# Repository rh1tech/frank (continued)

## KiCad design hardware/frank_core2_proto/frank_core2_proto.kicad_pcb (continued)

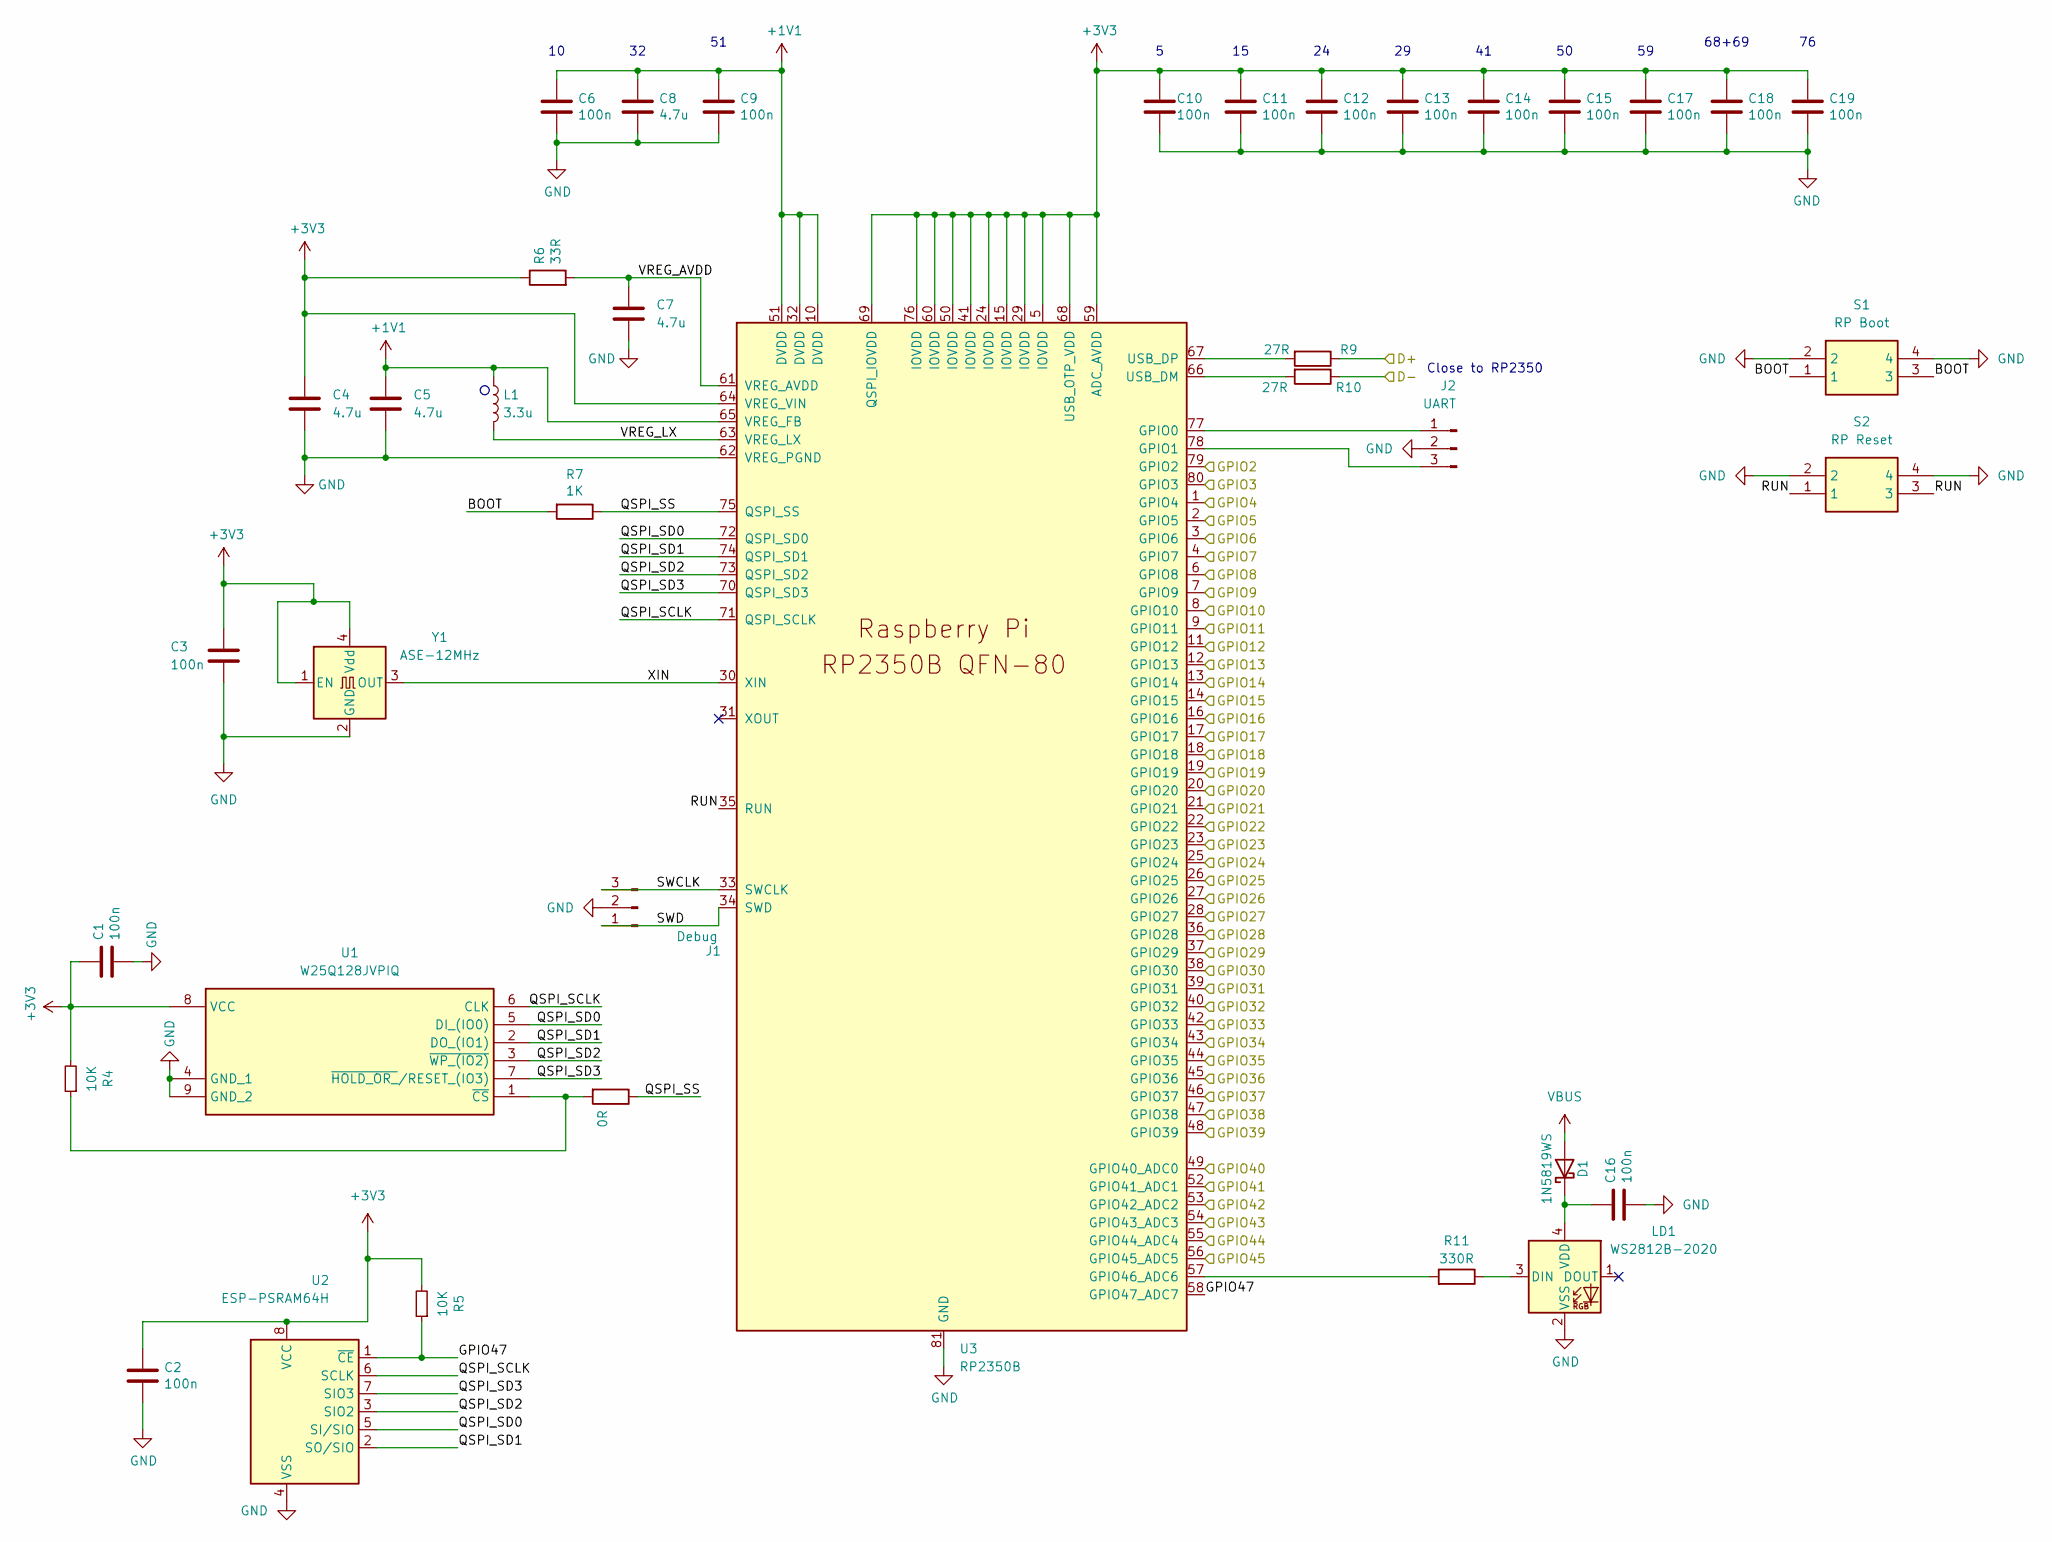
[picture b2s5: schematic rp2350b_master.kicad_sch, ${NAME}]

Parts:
C1, C2, C3, C6, C9, C10, C11, C12, C13, C14, C15, C16, C17, C18, C19: 100n; C_0603_1608Metric
C4, C5, C7, C8: 4.7u; C_0603_1608Metric
D1: 1N5819WS; D_SOD-323
J1: Debug; JST_SH_1x03_P1.00mm_Vertical
J2: UART; JST_SH_1x03_P1.00mm_Vertical
L1: 3.3u; L_Murata_LQH2MCN_2.0x1.6mm
LD1: WS2812B-2020; LED_WS2812B-2020_PLCC4_2.0x2.0mm
R4, R5: 10K; R_0603_1608Metric
R6: 33R; R_0603_1608Metric
R7: 1K; R_0603_1608Metric
R8: 0R; R_0603_1608Metric
R9, R10: 27R; R_0603_1608Metric
R11: 330R; R_0603_1608Metric
S1: RP Boot; SW_SPST_KMR2; Mouser Part Number 611-KMR221G-LFS
S2: RP Reset; SW_SPST_KMR2; Mouser Part Number 611-KMR221G-LFS
U1: W25Q128JVPIQ; WSON-8-1EP_6x5mm_P1.27mm_EP3.45x4.35mm; Mouser Part Number 454-W25Q128JVPIQ
U2: ESP-PSRAM64H; SOIC-8_3.9x4.9mm_P1.27mm
U3: RP2350B; QFN-80-1EP_10x10mm_P0.4mm_EP3.4x3.4mm
Y1: ASE-12MHz; Oscillator_SMD_3225-4Pin_3.2x2.5mm

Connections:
+1V1: C5.1, C6.1, C8.1, C9.1, L1.1, U3.10 (DVDD), U3.32 (DVDD), U3.51 (DVDD), U3.65 (VREG_FB)
+3V3: C1.1, C2.1, C3.1, C4.1, C10.1, C11.1, C12.1, C13.1, C14.1, C15.1, C17.1, C18.1, C19.1, R4.2, R5.2, R6.1, U1.8 (VCC), U2.8 (VCC), U3.5 (IOVDD), U3.15 (IOVDD), U3.24 (IOVDD), U3.29 (IOVDD), U3.41 (IOVDD), U3.50 (IOVDD), U3.59 (ADC_AVDD), U3.60 (IOVDD), U3.64 (VREG_VIN), U3.68 (USB_OTP_VDD), U3.69 (QSPI_IOVDD), U3.76 (IOVDD), Y1.1 (EN), Y1.4 (Vdd); also elsewhere on the board
/HDMI/CLKN/GPIO12: U3.11 (GPIO12); also elsewhere on the board
/HDMI/CLKP/GPIO13: U3.12 (GPIO13); also elsewhere on the board
/HDMI/D0N/GPIO14: U3.13 (GPIO14); also elsewhere on the board
/HDMI/D0P/GPIO15: U3.14 (GPIO15); also elsewhere on the board
/HDMI/D1N/GPIO16: U3.16 (GPIO16); also elsewhere on the board
/HDMI/D1P/GPIO17: U3.17 (GPIO17); also elsewhere on the board
/HDMI/D2N/GPIO18: U3.18 (GPIO18); also elsewhere on the board
/HDMI/D2P/GPIO19: U3.19 (GPIO19); also elsewhere on the board
/RP2350B/BOOT: R7.2, S1.1, S1.3
/RP2350B/GPIO2: U3.79 (GPIO2)
/RP2350B/GPIO3: U3.80 (GPIO3)
/RP2350B/GPIO8: U3.6 (GPIO8)
/RP2350B/GPIO28: U3.36 (GPIO28); also elsewhere on the board
/RP2350B/GPIO44: U3.55 (GPIO44_ADC4)
/RP2350B/GPIO45: U3.56 (GPIO45_ADC5)
/RP2350B/GPIO47: R5.1, U2.1 (~CE), U3.58 (GPIO47_ADC7)
/RP2350B/QSPI_SCLK: U1.6 (CLK), U2.6 (SCLK), U3.71 (QSPI_SCLK)
/RP2350B/QSPI_SD0: U1.5 (DI_(IO0)), U2.5 (SI/SIO), U3.72 (QSPI_SD0)
/RP2350B/QSPI_SD1: U1.2 (DO_(IO1)), U2.2 (SO/SIO), U3.74 (QSPI_SD1)
/RP2350B/QSPI_SD2: U1.3 (~WP_(IO2)), U2.3 (SIO2), U3.73 (QSPI_SD2)
/RP2350B/QSPI_SD3: U1.7 (~HOLD_OR_/RESET_(IO3)), U2.7 (SIO3), U3.70 (QSPI_SD3)
/RP2350B/QSPI_SS: R7.1, R8.1, U3.75 (QSPI_SS)
/RP2350B/RUN: S2.1, S2.3, U3.35 (RUN)
/RP2350B/SWCLK: J1.3, U3.33 (SWCLK)
/RP2350B/SWD: J1.1, U3.34 (SWD)
/RP2350B/VREG_AVDD: C7.1, R6.2, U3.61 (VREG_AVDD)
/RP2350B/VREG_LX: L1.2, U3.63 (VREG_LX)
/RP2350B/XIN: U3.30 (XIN), Y1.3 (OUT)
/RP2350B/D+: R9.1; also elsewhere on the board
/RP2350B/D-: R10.1; also elsewhere on the board
/RP2350/20B/1A/D0: U3.20 (GPIO20); also elsewhere on the board
/RP2350/21B/2A/D1: U3.21 (GPIO21); also elsewhere on the board
/RP2350/22B/3A/D2: U3.22 (GPIO22); also elsewhere on the board
/RP2350/23B/4A/D3: U3.23 (GPIO23); also elsewhere on the board
/RP2350/24B/5A/D4: U3.25 (GPIO24); also elsewhere on the board
/RP2350/25B/6A/D5: U3.26 (GPIO25); also elsewhere on the board
/RP2350/26B/7A/D6: U3.27 (GPIO26); also elsewhere on the board
/RP2350/27B/8A/D7: U3.28 (GPIO27); also elsewhere on the board
/RP2350/29B/10A/VALID: U3.37 (GPIO29); also elsewhere on the board
/RP2350/30B/11A/D0: U3.38 (GPIO30); also elsewhere on the board
/RP2350/31B/12A/D1: U3.39 (GPIO31); also elsewhere on the board
/RP2350/32B/13A/D2: U3.40 (GPIO32); also elsewhere on the board
/RP2350/33B/14A/D3: U3.42 (GPIO33); also elsewhere on the board
/RP2350/34B/15A/D4: U3.43 (GPIO34); also elsewhere on the board
/RP2350/35B/16A/D5: U3.44 (GPIO35); also elsewhere on the board
/RP2350/36B/17A/D6: U3.45 (GPIO36); also elsewhere on the board
/RP2350/37B/18A/D7: U3.46 (GPIO37); also elsewhere on the board
/RP2350/38B/19A/CLK: U3.47 (GPIO38); also elsewhere on the board
/RP2350/39B/20A/VALID: U3.48 (GPIO39); also elsewhere on the board
/RP2350/40B/21A/FS: U3.49 (GPIO40_ADC0); also elsewhere on the board
/RP2350/41B/22A/DB_MS: U3.52 (GPIO41_ADC1); also elsewhere on the board
/RP2350/42B/23A/DB_SM: U3.53 (GPIO42_ADC2); also elsewhere on the board
/RP2350/43B/RUNA/SR: U3.54 (GPIO43_ADC3); also elsewhere on the board
/SD/CDDAT3/GPIO5: U3.2 (GPIO5); also elsewhere on the board
/SD/CLK/GPIO6: U3.3 (GPIO6); also elsewhere on the board
/SD/CMD/GPIO7: U3.4 (GPIO7); also elsewhere on the board
/SD/DAT0/GPIO4: U3.1 (GPIO4); also elsewhere on the board
/TDA/DATA/GPIO9: U3.7 (GPIO9); also elsewhere on the board
/TDA/LRCK/GPIO11: U3.9 (GPIO11); also elsewhere on the board
/TDA/SCLK/GPIO10: U3.8 (GPIO10); also elsewhere on the board
GND: C1.2, C2.2, C3.2, C4.2, C5.2, C6.2, C7.2, C8.2, C9.2, C10.2, C11.2, C12.2, C13.2, C14.2, C15.2, C16.2, C17.2, C18.2, C19.2, J1.2, J2.2, LD1.2 (VSS), S1.2, S1.4, S2.2, S2.4, U1.4 (GND_1), U1.9 (GND_2), U2.4 (VSS), U3.62 (VREG_PGND), U3.81 (GND), Y1.2 (GND); also elsewhere on the board
unnamed: C16.1, D1.1 (K), LD1.4 (VDD)
unnamed: J2.1, U3.77 (GPIO0)
unnamed: J2.3, U3.78 (GPIO1)
unnamed: LD1.3 (DIN), R11.1
unnamed: R4.1, R8.2, U1.1 (~CS)
unnamed: R11.2, U3.57 (GPIO46_ADC6)
unnamed: R10.2, U3.66 (USB_DM)
unnamed: R9.2, U3.67 (USB_DP)
VBUS: D1.2 (A); also elsewhere on the board

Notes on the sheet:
Close to RP2350
68+69

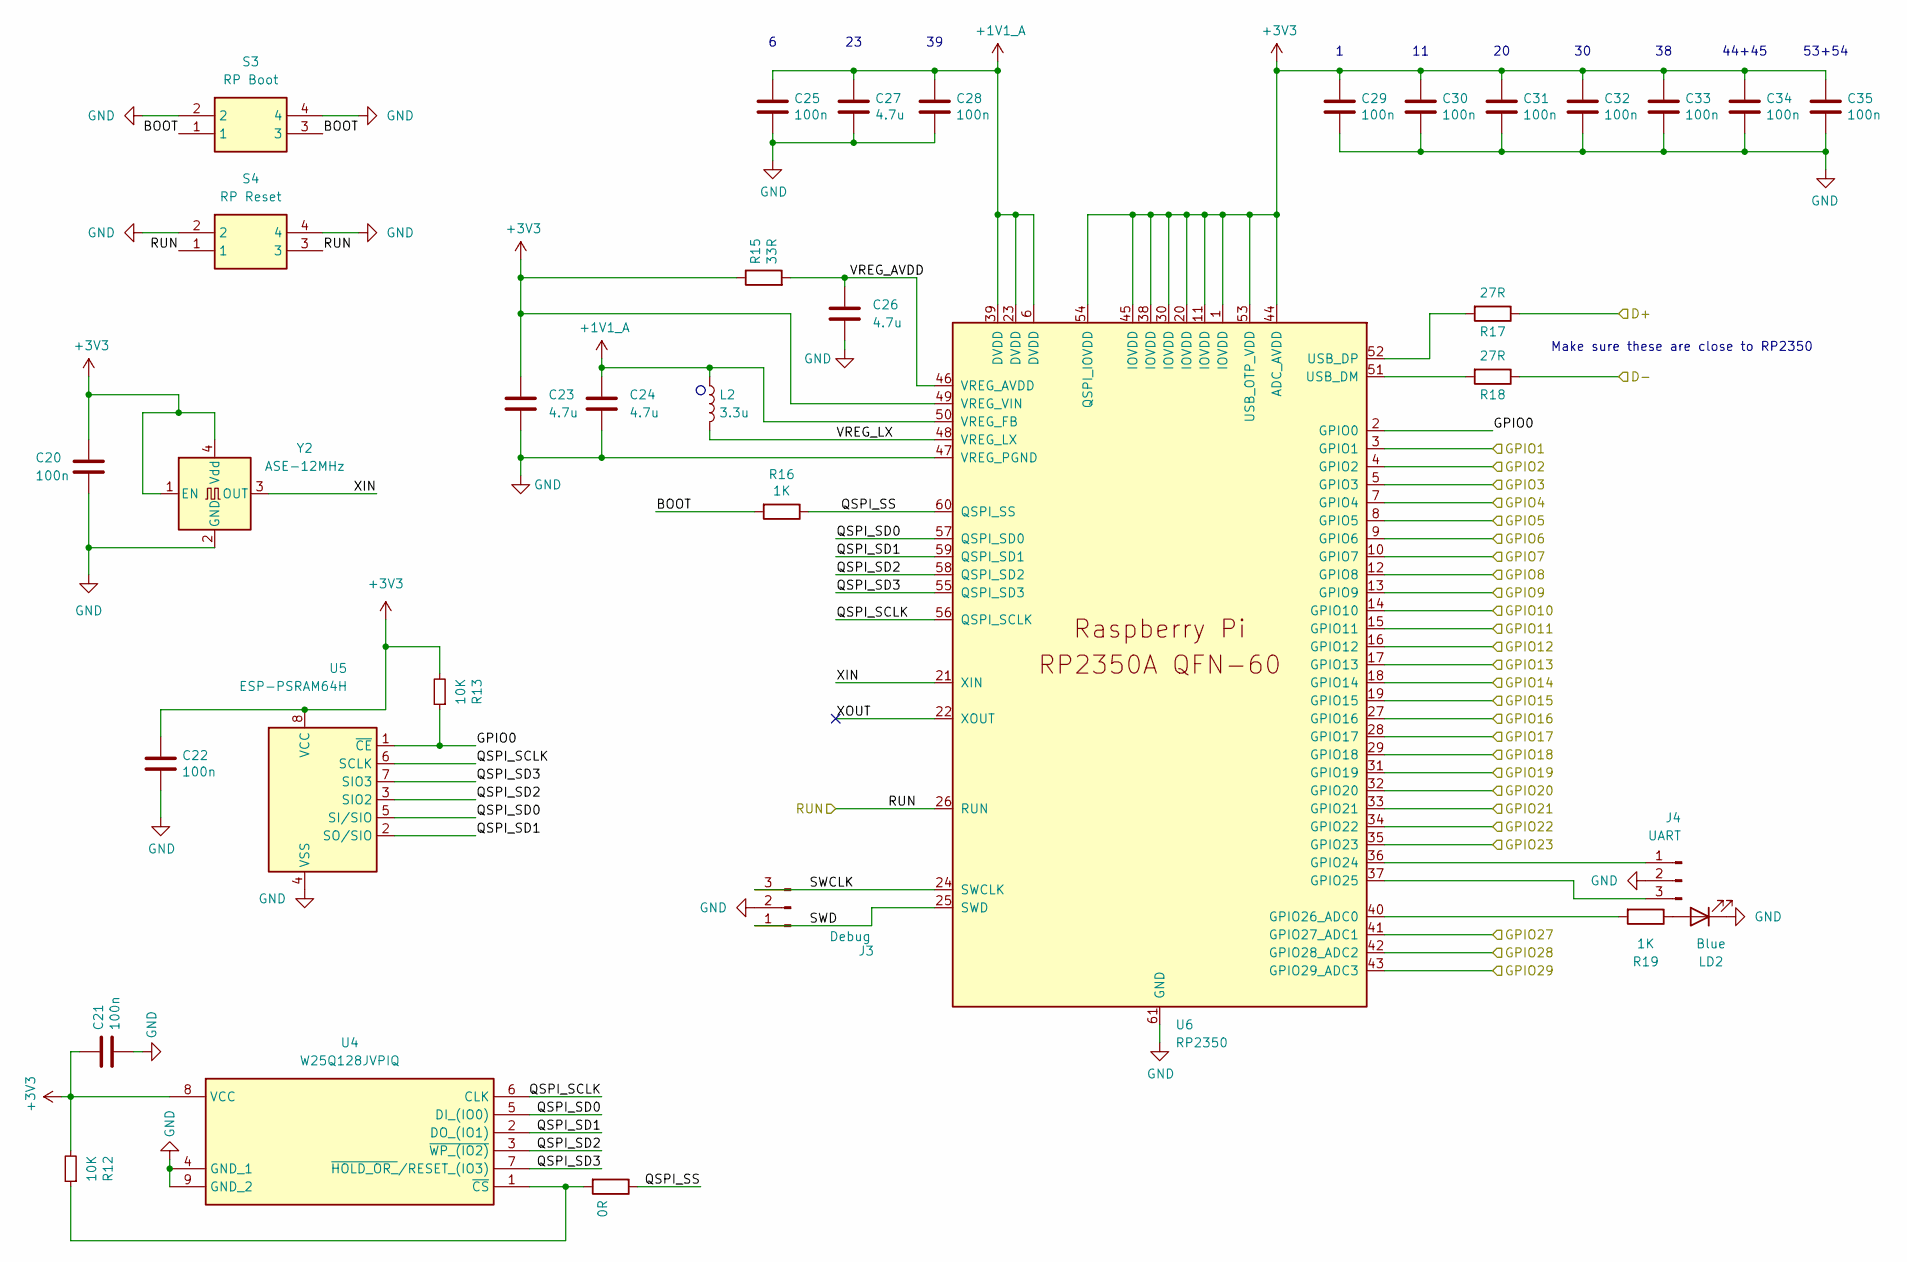
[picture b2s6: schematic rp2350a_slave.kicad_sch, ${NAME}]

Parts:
C20, C21, C22, C25, C28, C29, C30, C31, C32, C33, C34, C35: 100n; C_0603_1608Metric
C23, C24, C26, C27: 4.7u; C_0603_1608Metric
J3: Debug; JST_SH_1x03_P1.00mm_Vertical
J4: UART; JST_SH_1x03_P1.00mm_Vertical
L2: 3.3u; L_AOTA-B201610_2.0x1.6mm
LD2: Blue; LED_0603_1608Metric
R12, R13: 10K; R_0603_1608Metric
R14: 0R; R_0603_1608Metric
R15: 33R; R_0603_1608Metric
R16, R19: 1K; R_0603_1608Metric
R17, R18: 27R; R_0603_1608Metric
S3: RP Boot; SW_SPST_KMR2; Mouser Part Number 611-KMR221G-LFS
S4: RP Reset; SW_SPST_KMR2; Mouser Part Number 611-KMR221G-LFS
U4: W25Q128JVPIQ; WSON-8-1EP_6x5mm_P1.27mm_EP3.45x4.35mm; Mouser Part Number 454-W25Q128JVPIQ
U5: ESP-PSRAM64H; SOIC-8_3.9x4.9mm_P1.27mm
U6: RP2350; QFN-60-1EP_7x7mm_P0.4mm_EP3.4x3.4mm
Y2: ASE-12MHz; Oscillator_SMD_Abracon_ASE-4Pin_3.2x2.5mm

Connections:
+1V1_A: C24.1, C25.1, C27.1, C28.1, L2.1, U6.6 (DVDD), U6.23 (DVDD), U6.39 (DVDD), U6.50 (VREG_FB)
+3V3: C20.1, C21.1, C22.1, C23.1, C29.1, C30.1, C31.1, C32.1, C33.1, C34.1, C35.1, R12.2, R13.2, R15.1, U4.8 (VCC), U5.8 (VCC), U6.1 (IOVDD), U6.11 (IOVDD), U6.20 (IOVDD), U6.30 (IOVDD), U6.38 (IOVDD), U6.44 (ADC_AVDD), U6.45 (IOVDD), U6.49 (VREG_VIN), U6.53 (USB_OTP_VDD), U6.54 (QSPI_IOVDD), Y2.1 (EN), Y2.4 (Vdd); also elsewhere on the board
/RP2350A/BOOT: R16.2, S3.1, S3.3
/RP2350A/GPIO0: R13.1, U5.1 (~CE), U6.2 (GPIO0)
/RP2350A/GPIO19: U6.31 (GPIO19); also elsewhere on the board
/RP2350A/GPIO27: U6.41 (GPIO27_ADC1)
/RP2350A/GPIO28: U6.42 (GPIO28_ADC2)
/RP2350A/GPIO29: U6.43 (GPIO29_ADC3)
/RP2350A/QSPI_SCLK: U4.6 (CLK), U5.6 (SCLK), U6.56 (QSPI_SCLK)
/RP2350A/QSPI_SD0: U4.5 (DI_(IO0)), U5.5 (SI/SIO), U6.57 (QSPI_SD0)
/RP2350A/QSPI_SD1: U4.2 (DO_(IO1)), U5.2 (SO/SIO), U6.59 (QSPI_SD1)
/RP2350A/QSPI_SD2: U4.3 (~WP_(IO2)), U5.3 (SIO2), U6.58 (QSPI_SD2)
/RP2350A/QSPI_SD3: U4.7 (~HOLD_OR_/RESET_(IO3)), U5.7 (SIO3), U6.55 (QSPI_SD3)
/RP2350A/QSPI_SS: R14.1, R16.1, U6.60 (QSPI_SS)
/RP2350A/SWCLK: J3.3, U6.24 (SWCLK)
/RP2350A/SWD: J3.1, U6.25 (SWD)
/RP2350A/VREG_AVDD: C26.1, R15.2, U6.46 (VREG_AVDD)
/RP2350A/VREG_LX: L2.2, U6.48 (VREG_LX)
/RP2350A/XIN: U6.21 (XIN), Y2.3 (OUT)
/RP2350A/XOUT: U6.22 (XOUT)
/RP2350A/D+: R17.1; also elsewhere on the board
/RP2350A/D-: R18.1; also elsewhere on the board
/RP2350/20B/1A/D0: U6.3 (GPIO1); also elsewhere on the board
/RP2350/21B/2A/D1: U6.4 (GPIO2); also elsewhere on the board
/RP2350/22B/3A/D2: U6.5 (GPIO3); also elsewhere on the board
/RP2350/23B/4A/D3: U6.7 (GPIO4); also elsewhere on the board
/RP2350/24B/5A/D4: U6.8 (GPIO5); also elsewhere on the board
/RP2350/25B/6A/D5: U6.9 (GPIO6); also elsewhere on the board
/RP2350/26B/7A/D6: U6.10 (GPIO7); also elsewhere on the board
/RP2350/27B/8A/D7: U6.12 (GPIO8); also elsewhere on the board
/RP2350/28B/9A/CLK: U6.13 (GPIO9); also elsewhere on the board
/RP2350/29B/10A/VALID: U6.14 (GPIO10); also elsewhere on the board
/RP2350/30B/11A/D0: U6.15 (GPIO11); also elsewhere on the board
/RP2350/31B/12A/D1: U6.16 (GPIO12); also elsewhere on the board
/RP2350/32B/13A/D2: U6.17 (GPIO13); also elsewhere on the board
/RP2350/33B/14A/D3: U6.18 (GPIO14); also elsewhere on the board
/RP2350/34B/15A/D4: U6.19 (GPIO15); also elsewhere on the board
/RP2350/35B/16A/D5: U6.27 (GPIO16); also elsewhere on the board
/RP2350/36B/17A/D6: U6.28 (GPIO17); also elsewhere on the board
/RP2350/37B/18A/D7: U6.29 (GPIO18); also elsewhere on the board
/RP2350/39B/20A/VALID: U6.32 (GPIO20); also elsewhere on the board
/RP2350/40B/21A/FS: U6.33 (GPIO21); also elsewhere on the board
/RP2350/41B/22A/DB_MS: U6.34 (GPIO22); also elsewhere on the board
/RP2350/42B/23A/DB_SM: U6.35 (GPIO23); also elsewhere on the board
/RP2350/43B/RUNA/SR: S4.1, S4.3, U6.26 (RUN); also elsewhere on the board
GND: C20.2, C21.2, C22.2, C23.2, C24.2, C25.2, C26.2, C27.2, C28.2, C29.2, C30.2, C31.2, C32.2, C33.2, C34.2, C35.2, J3.2, J4.2, LD2.1 (K), S3.2, S3.4, S4.2, S4.4, U4.4 (GND_1), U4.9 (GND_2), U5.4 (VSS), U6.47 (VREG_PGND), U6.61 (GND), Y2.2 (GND); also elsewhere on the board
unnamed: J4.1, U6.36 (GPIO24)
unnamed: J4.3, U6.37 (GPIO25)
unnamed: LD2.2 (A), R19.1
unnamed: R12.1, R14.2, U4.1 (~CS)
unnamed: R19.2, U6.40 (GPIO26_ADC0)
unnamed: R18.2, U6.51 (USB_DM)
unnamed: R17.2, U6.52 (USB_DP)

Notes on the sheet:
44+45
Make sure these are close to RP2350
53+54

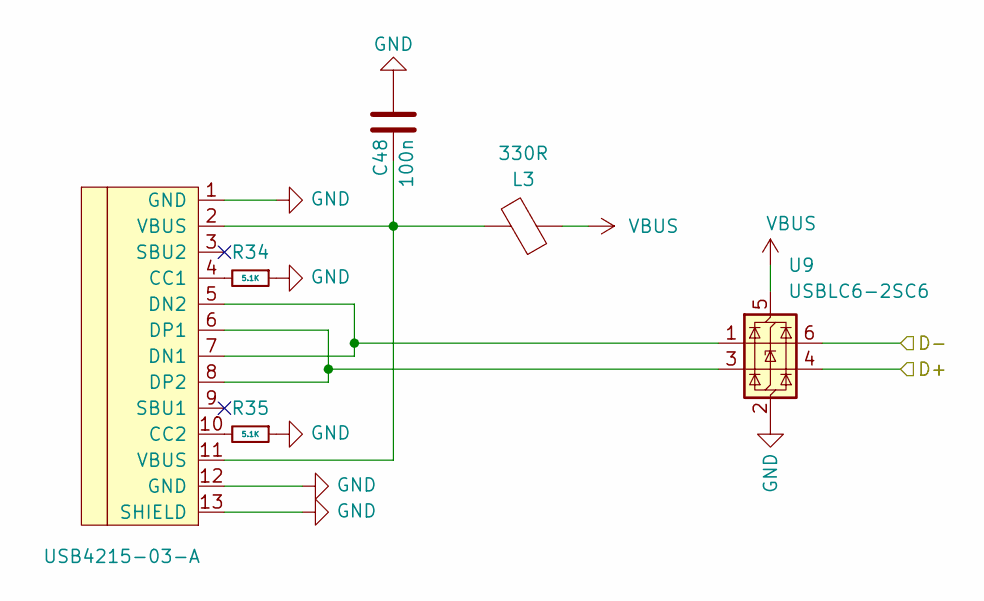
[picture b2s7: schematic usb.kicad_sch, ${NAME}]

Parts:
C48: 100n; C_0603_1608Metric
J8: USB4215-03-A; USB_C_Receptacle; LCSC C165948
L3: 330R; L_0603_1608Metric
R34, R35: 5.1K; R_0603_1608Metric
U9: USBLC6-2SC6; SOT-23-6

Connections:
/RP2350B/D+: U9.4 (I/O2); also elsewhere on the board
/RP2350B/D-: U9.6 (I/O1); also elsewhere on the board
GND: C48.2, J8.1 (GND), J8.12 (GND), J8.13 (SHIELD), R34.1, R35.1, U9.2 (GND); also elsewhere on the board
unnamed: C48.1, J8.2 (VBUS), J8.11 (VBUS), L3.2
unnamed: J8.4 (CC1), R34.2
unnamed: J8.10 (CC2), R35.2
unnamed: J8.5 (DN2), J8.7 (DN1), U9.1 (I/O1)
unnamed: J8.6 (DP1), J8.8 (DP2), U9.3 (I/O2)
VBUS: L3.1, U9.5 (VBUS); also elsewhere on the board

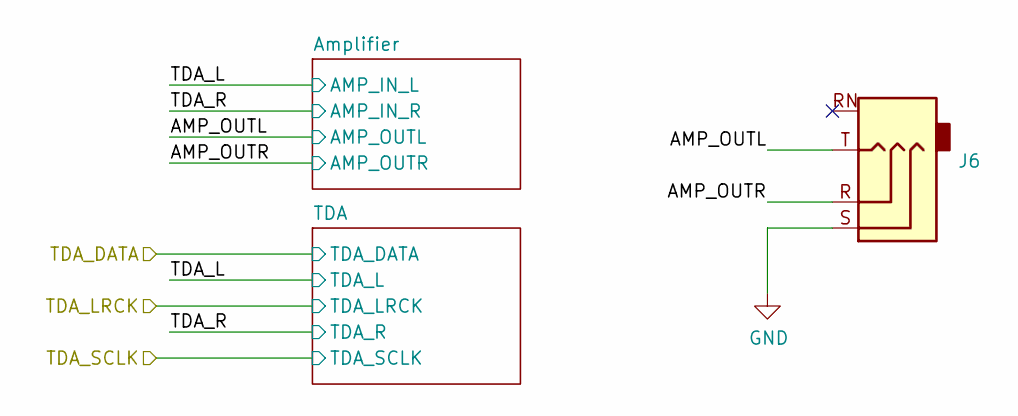
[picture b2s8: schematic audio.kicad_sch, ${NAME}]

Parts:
J6: PJ-320D; AudioJack_3.5mm_PJ320D_AudioOut

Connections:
/TDA Audio/AMP_OUTL: J6.T; also elsewhere on the board
/TDA Audio/AMP_OUTR: J6.R; also elsewhere on the board
GND: J6.S; also elsewhere on the board

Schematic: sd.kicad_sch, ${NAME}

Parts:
C47: 100n; C_0603_1608Metric
J7: 104031-0811; MicroSD_SMD_Long

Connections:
+3V3: C47.2, J7.4 (VDD); also elsewhere on the board
/SD/CDDAT3/GPIO5: J7.2 (DAT3/CD); also elsewhere on the board
/SD/CLK/GPIO6: J7.5 (CLK); also elsewhere on the board
/SD/CMD/GPIO7: J7.3 (CMD); also elsewhere on the board
/SD/DAT0/GPIO4: J7.7 (DAT0); also elsewhere on the board
GND: C47.1, J7.6 (VSS); also elsewhere on the board

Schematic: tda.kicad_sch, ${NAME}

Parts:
C44, C46: 10u; C_0603_1608Metric
C45: 100n; C_0603_1608Metric
R31: 100R; R_0603_1608Metric
R32, R33: 470R; R_0603_1608Metric
U8: TDA1387T; SOIC-8_3.9x4.9mm_P1.27mm

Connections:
/TDA Audio/TDA_L: R33.2, U8.6 (A_LEFT); also elsewhere on the board
/TDA Audio/TDA_R: R32.1, U8.8 (A_RIGHT); also elsewhere on the board
/TDA/DATA/GPIO9: U8.3 (DATA); also elsewhere on the board
/TDA/LRCK/GPIO11: U8.2 (LRCK); also elsewhere on the board
/TDA/SCLK/GPIO10: U8.1 (SCLK); also elsewhere on the board
GND: C44.2, C45.2, C46.2, R32.2, R33.1, U8.4 (AGND); also elsewhere on the board
unnamed: C46.1, U8.7 (FLT)
unnamed: C44.1, C45.1, R31.1, U8.5 (VA)
VBUS: R31.2; also elsewhere on the board

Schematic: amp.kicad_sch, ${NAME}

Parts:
C37, C38, C39, C41, C42: 10u; C_0603_1608Metric
C40: 10u; CP_EIA-3528-12_Kemet-T
C43: 100n; C_0603_1608Metric
R20, R21, R22, R23, R24, R25: 10K; R_0603_1608Metric
R26, R27: 47K; R_0603_1608Metric
R28, R29: 20K; R_0603_1608Metric
R30: 100R; R_0603_1608Metric
U7: LM358; SOIC-8_3.9x4.9mm_P1.27mm

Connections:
/TDA Audio/AMP_OUTL: C41.2, R28.2; also elsewhere on the board
/TDA Audio/AMP_OUTR: C42.2, R29.2; also elsewhere on the board
/TDA Audio/TDA_L: C37.1, R20.1; also elsewhere on the board
/TDA Audio/TDA_R: C38.1, R21.1; also elsewhere on the board
GND: C39.1, C40.2, C43.1, R20.2, R21.2, R23.1, R28.1, R29.1, U7.4 (V-); also elsewhere on the board
unnamed: C37.2, R24.2
unnamed: C38.2, R25.2
unnamed: C41.1, R26.1, U7.7
unnamed: C42.1, R27.1, U7.1
unnamed: C39.2, R22.1, R23.2, U7.3 (+), U7.5 (+)
unnamed: R25.1, R27.2, U7.2 (-)
unnamed: R24.1, R26.2, U7.6 (-)
unnamed: C40.1, C43.2, R22.2, R30.2, U7.8 (V+)
VBUS: R30.1; also elsewhere on the board

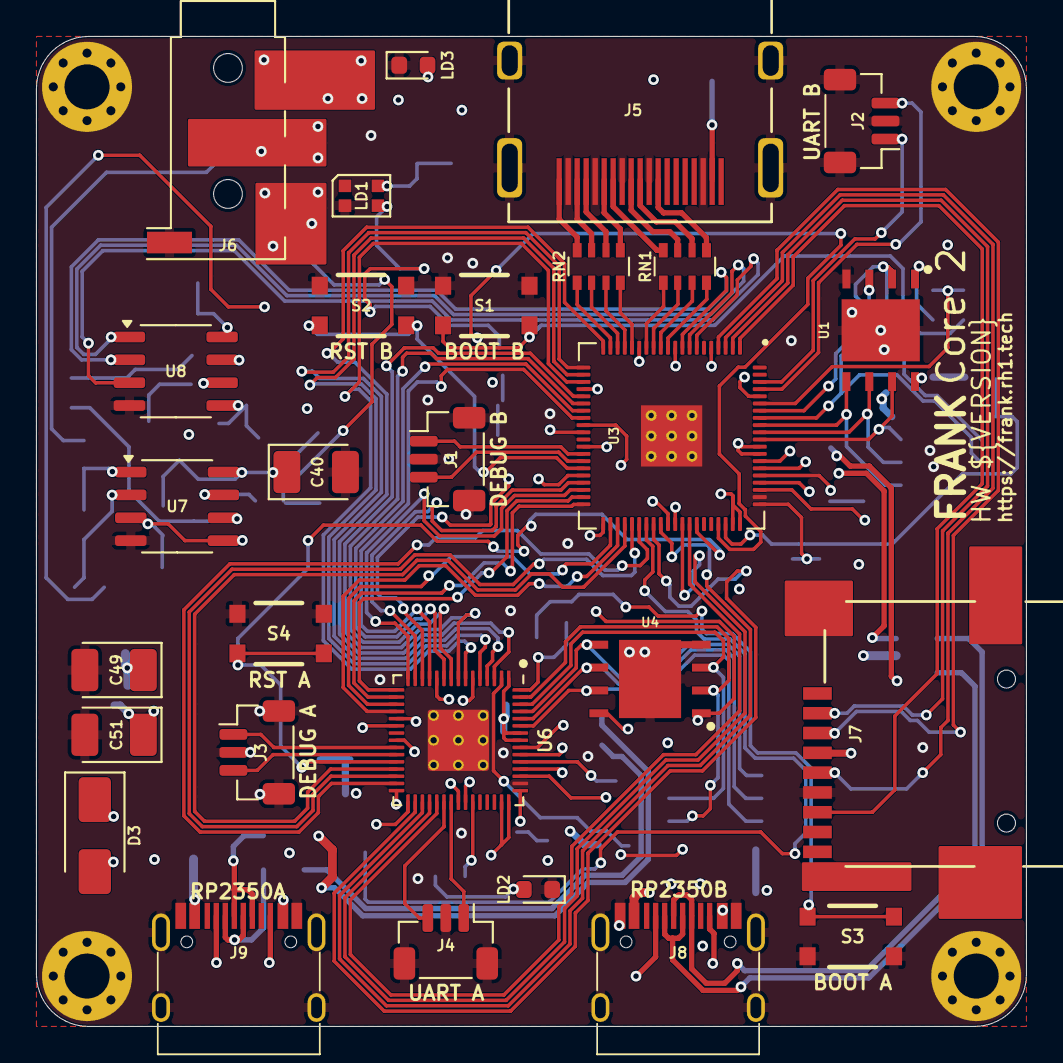
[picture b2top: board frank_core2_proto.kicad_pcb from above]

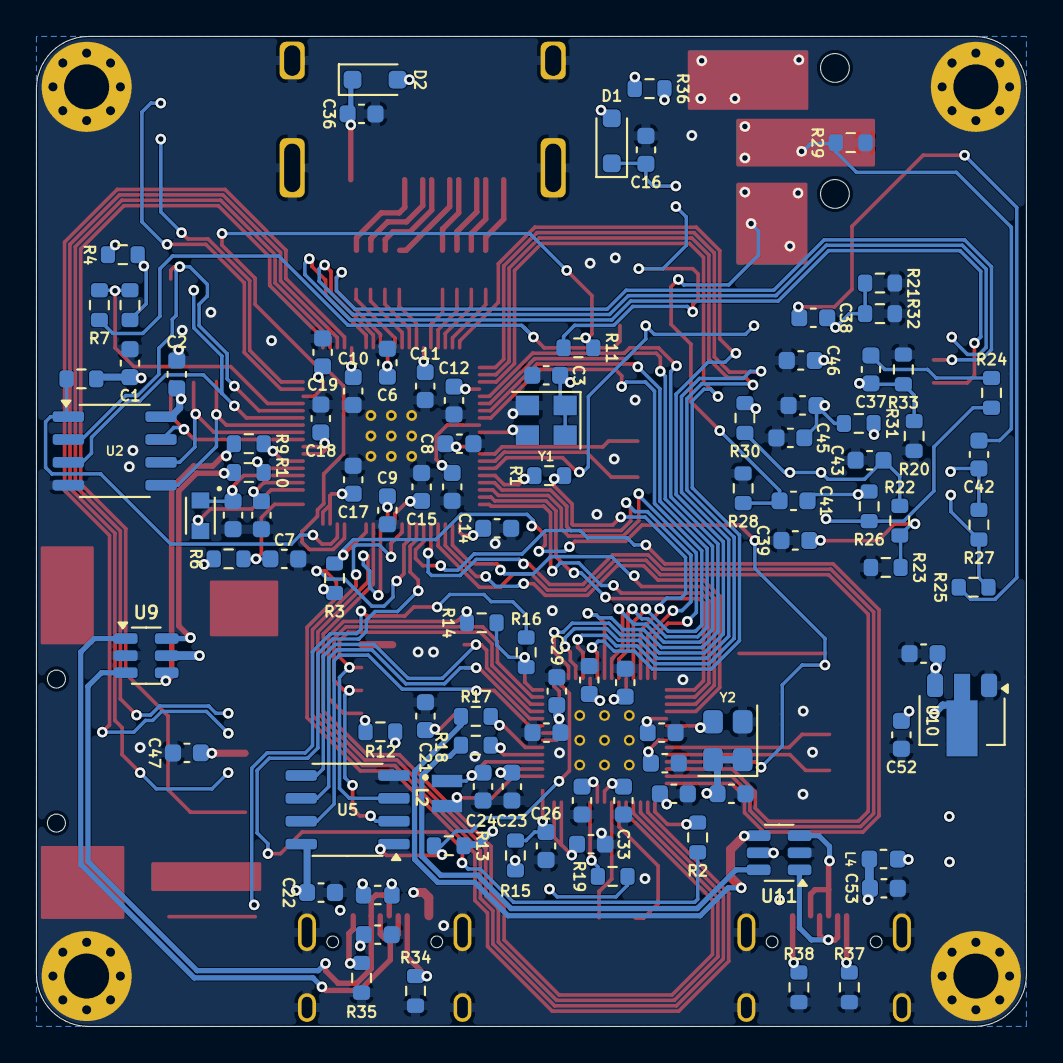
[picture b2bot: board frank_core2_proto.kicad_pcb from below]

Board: 4 copper layers, 55.0 x 55.0 mm, 133 parts (101 on the bottom side), 127 nets.
